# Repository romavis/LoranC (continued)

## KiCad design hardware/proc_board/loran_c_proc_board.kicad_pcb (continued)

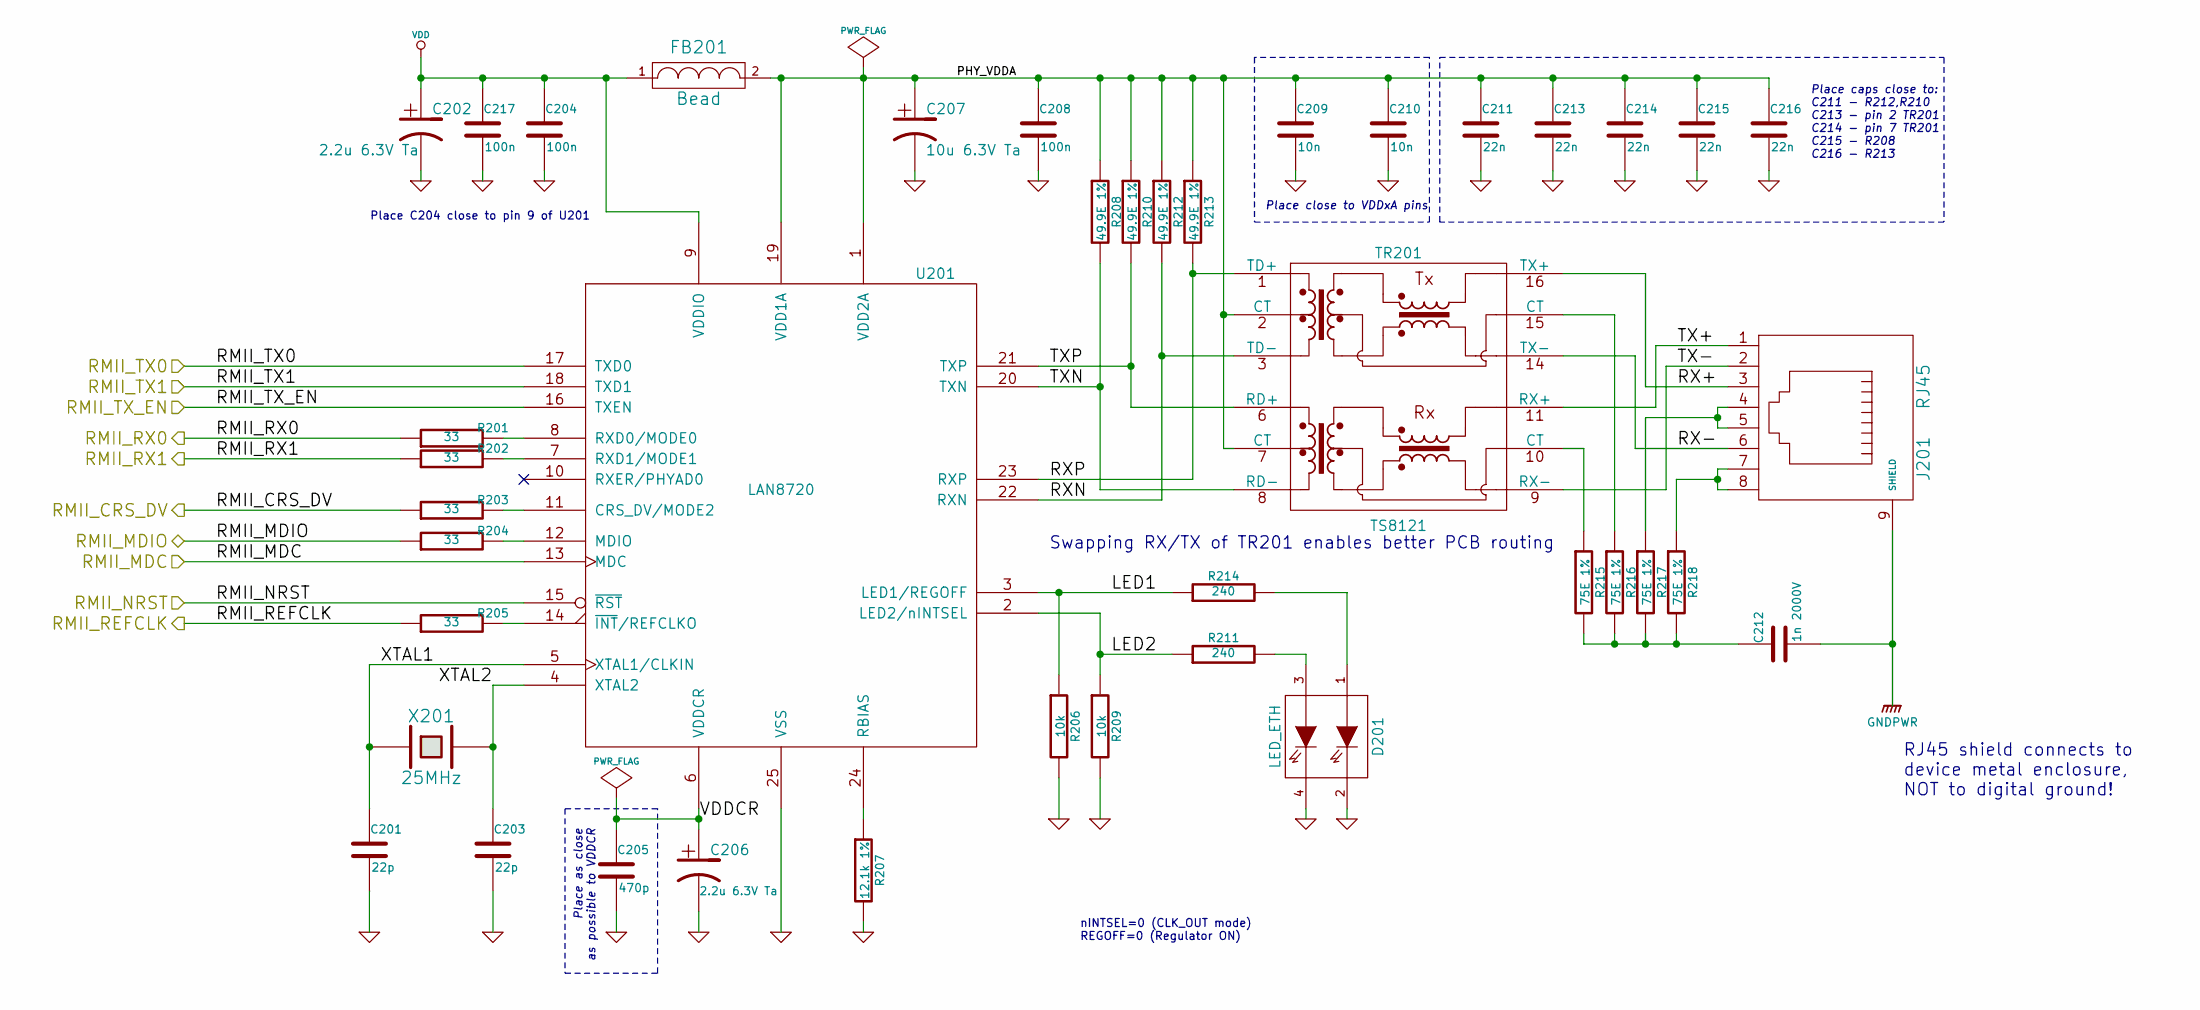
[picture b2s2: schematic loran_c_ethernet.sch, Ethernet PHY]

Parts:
C201, C203: 22p; r_0805
C202, C206: 2.2u 6.3V Ta; c_tant_A
C204, C208, C217: 100n; c_1206
C205: 470p; r_0805
C207: 10u 6.3V Ta; c_tant_B
C209, C210: 10n; c_1206
C211, C213, C214, C215, C216: 22n; c_1206
C212: 1n 2000V; cnp_6mm_disc
D201: LED_ETH
FB201: Bead; RC07
J201: RJ45; RJ45_8
R201, R202: 33; r_1206
R203, R204, R205: 33; r_0805
R206, R209: 10k; r_1206
R207: 12.1k 1%; r_1206
R208, R210, R212, R213: 49.9E 1%; r_1206
R211, R214: 240; r_1206
R215, R216, R217, R218: 75E 1%; r_1206
TR201: TS8121
U201: LAN8720; qfn-24
X201: 25MHz; crystal_hc-49u

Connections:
/Ethernet PHY/LED1: R206.1, R214.1, U201.3 (LED1/REGOFF)
/Ethernet PHY/LED2: R209.1, R211.1, U201.2 (LED2/nINTSEL)
/Ethernet PHY/PHY_VDDA: C207.1, C208.1, C209.1, C210.1, C211.1, C213.1, C214.1, C215.1, C216.1, FB201.2, R208.1, R210.1, R212.1, R213.1, TR201.2 (CT), TR201.7 (CT), U201.1 (VDD2A), U201.19 (VDD1A)
/Ethernet PHY/RMII_CRS_DV: R203.1; also elsewhere on the board
/Ethernet PHY/RMII_MDC: U201.13 (MDC); also elsewhere on the board
/Ethernet PHY/RMII_MDIO: R204.1; also elsewhere on the board
/Ethernet PHY/RMII_NRST: U201.15 (~RST); also elsewhere on the board
/Ethernet PHY/RMII_REFCLK: R205.1; also elsewhere on the board
/Ethernet PHY/RMII_RX0: R201.1; also elsewhere on the board
/Ethernet PHY/RMII_RX1: R202.1; also elsewhere on the board
/Ethernet PHY/RMII_TX0: U201.17 (TXD0); also elsewhere on the board
/Ethernet PHY/RMII_TX1: U201.18 (TXD1); also elsewhere on the board
/Ethernet PHY/RMII_TX_EN: U201.16 (TXEN); also elsewhere on the board
/Ethernet PHY/RX+: J201.3, TR201.16 (TX+)
/Ethernet PHY/RX-: J201.6, TR201.14 (TX-)
/Ethernet PHY/RXN: R212.2, TR201.3 (TD-), U201.22 (RXN)
/Ethernet PHY/RXP: R213.2, TR201.1 (TD+), U201.23 (RXP)
/Ethernet PHY/TX+: J201.1, TR201.11 (RX+)
/Ethernet PHY/TX-: J201.2, TR201.9 (RX-)
/Ethernet PHY/TXN: R208.2, TR201.8 (RD-), U201.20 (TXN)
/Ethernet PHY/TXP: R210.2, TR201.6 (RD+), U201.21 (TXP)
/Ethernet PHY/VDDCR: C205.1, C206.1, U201.6 (VDDCR)
/Ethernet PHY/XTAL1: C201.1, U201.5 (XTAL1/CLKIN), X201.1
/Ethernet PHY/XTAL2: C203.1, U201.4 (XTAL2), X201.2
GND: C201.2, C202.2, C203.2, C204.2, C205.2, C206.2, C207.2, C208.2, C209.2, C210.2, C211.2, C213.2, C214.2, C215.2, C216.2, C217.2, D201.2 (K1), D201.4 (K2), R206.2, R207.2, R209.2, U201.25 (VSS); also elsewhere on the board
GNDPWR: C212.2, J201.9 (SHIELD); also elsewhere on the board
unnamed: C212.1, R215.2, R216.2, R217.2, R218.2
unnamed: D201.1 (A1), R214.2
unnamed: D201.3 (A2), R211.2
unnamed: J201.4, J201.5, R217.1
unnamed: J201.7, J201.8, R218.1
unnamed: R201.2, U201.8 (RXD0/MODE0)
unnamed: R202.2, U201.7 (RXD1/MODE1)
unnamed: R203.2, U201.11 (CRS_DV/MODE2)
unnamed: R204.2, U201.12 (MDIO)
unnamed: R205.2, U201.14 (~INT~/REFCLKO)
unnamed: R207.1, U201.24 (RBIAS)
unnamed: R215.1, TR201.10 (CT)
unnamed: R216.1, TR201.15 (CT)
VDD: C202.1, C204.1, C217.1, FB201.1, U201.9 (VDDIO); also elsewhere on the board

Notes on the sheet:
nINTSEL=0 (CLK_OUT mode) REGOFF=0 (Regulator ON)
Place caps close to: C211 - R212,R210 C213 - pin 2 TR201 C214 - pin 7 TR201 C215 - R208 C216 - R213
Place as close as possible to VDDCR
Place close to VDDxA pins
RJ45 shield connects to device metal enclosure, NOT to digital ground!
Swapping RX/TX of TR201 enables better PCB routing
Place C204 close to pin 9 of U201

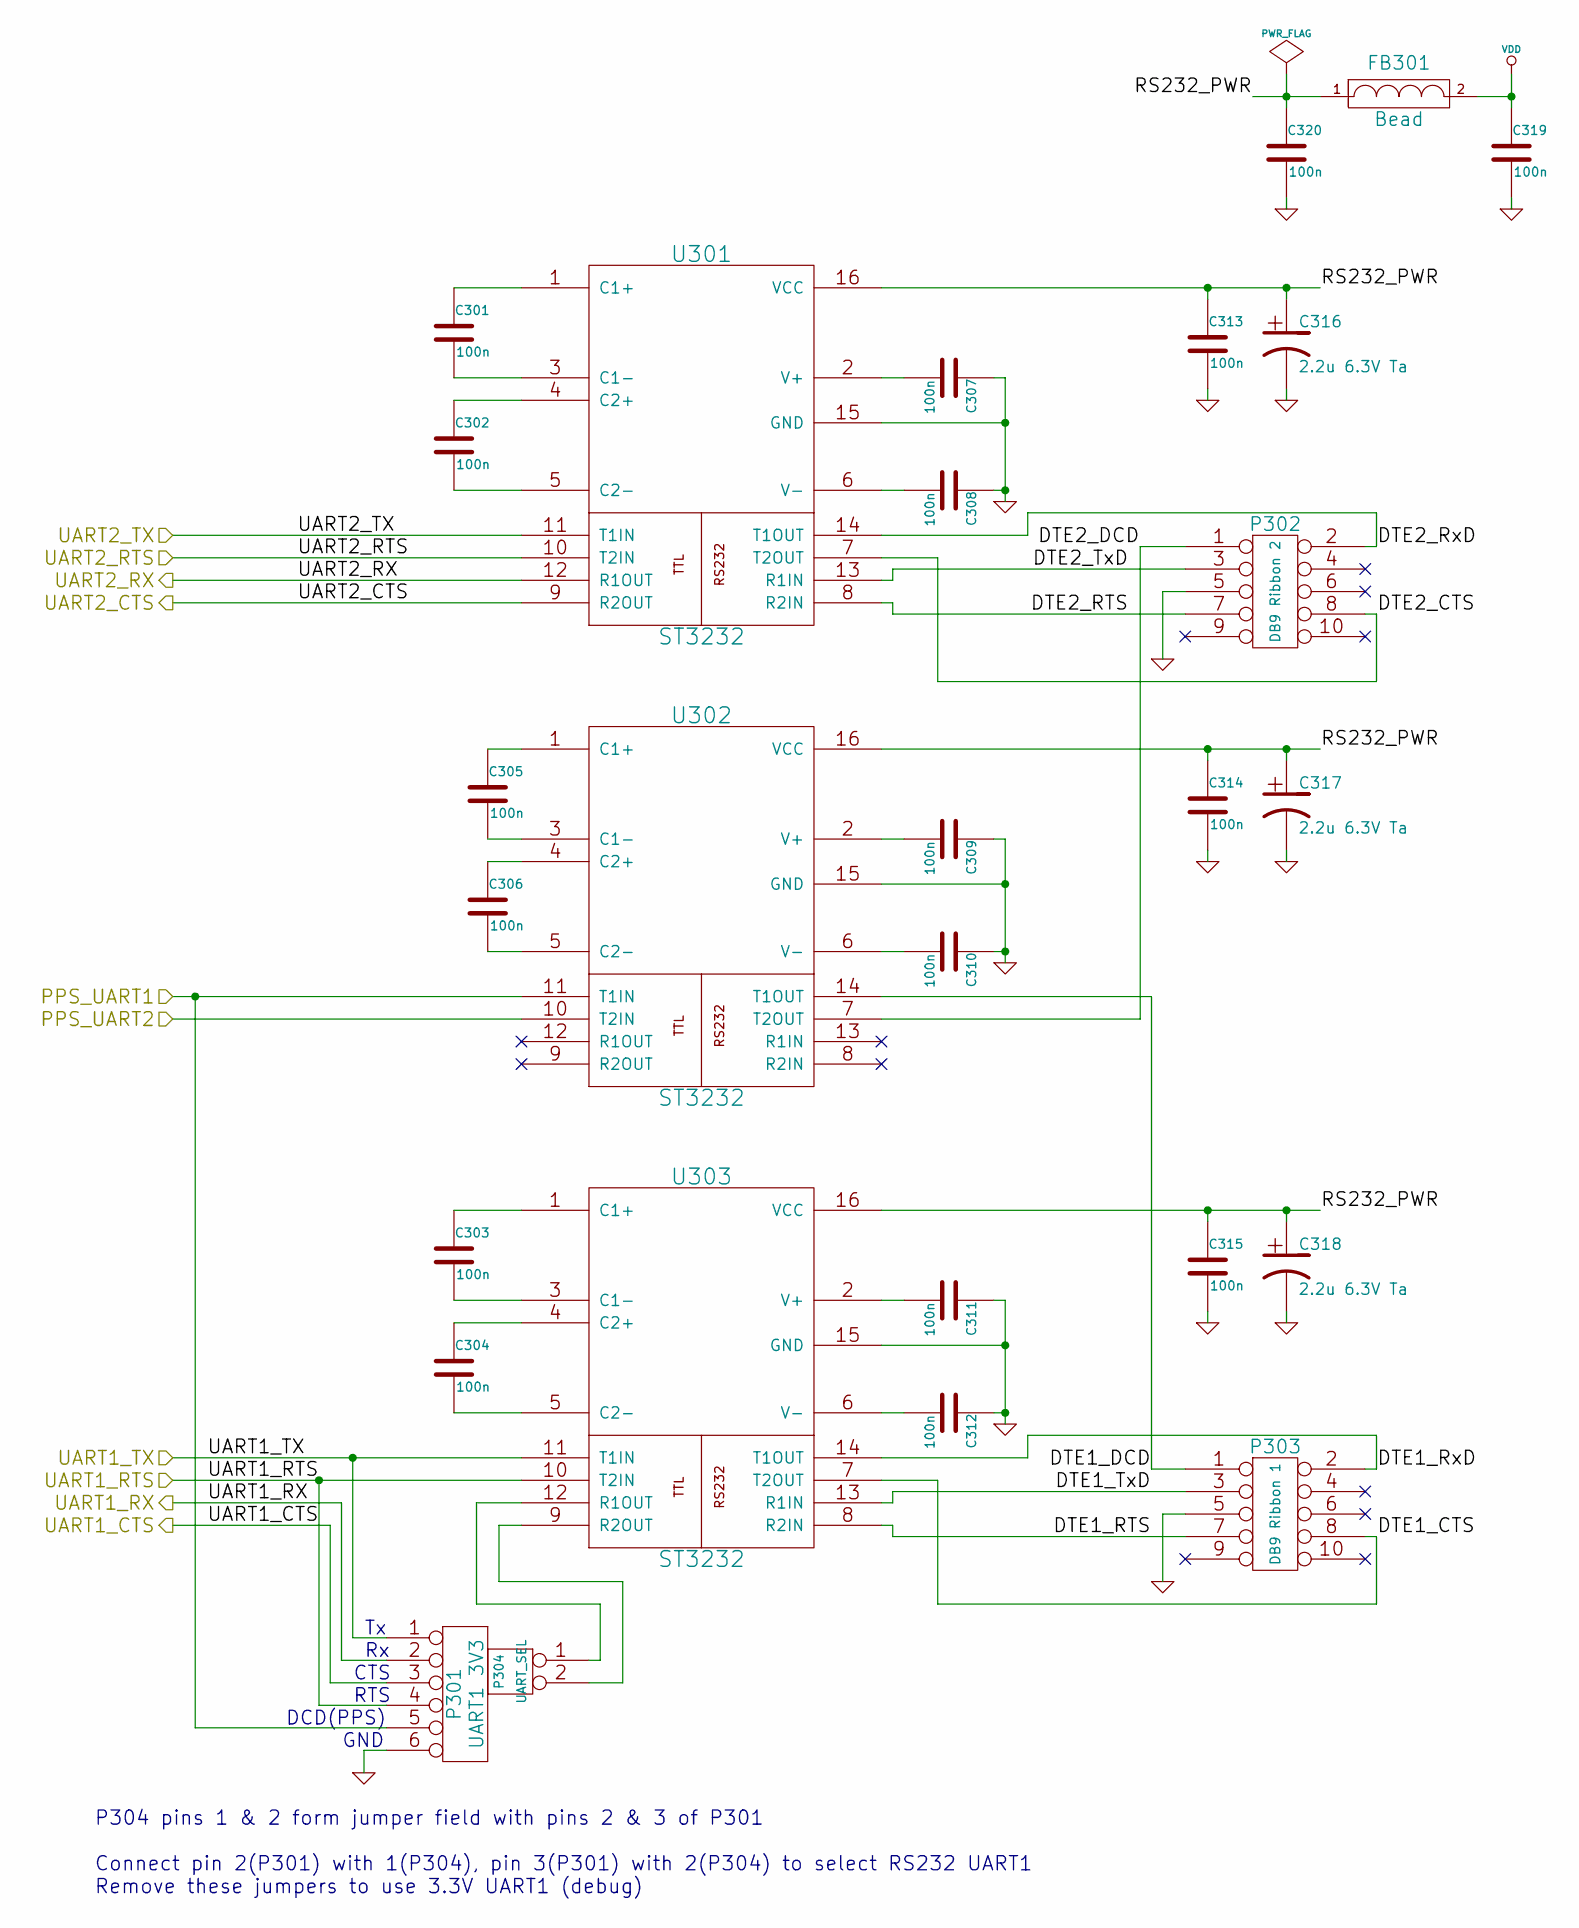
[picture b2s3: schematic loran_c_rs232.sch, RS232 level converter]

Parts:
C301, C302, C303, C304, C305, C306, C307, C308, C309, C310, C311, C312, C313, C314, C315, C319, C320: 100n; c_1206
C316, C317, C318: 2.2u 6.3V Ta; c_tant_A
FB301: Bead; RC07
P301: UART1 3V3; Pin_Header_Straight_1x06
P302: DB9 Ribbon 2; vasch_strip_5x2
P303: DB9 Ribbon 1; vasch_strip_5x2
P304: UART_SEL; Pin_Header_Straight_1x02
U301, U302, U303: ST3232; so-16

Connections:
/RS232 interface/DTE1_CTS: P303.8, U303.7 (T2OUT)
/RS232 interface/DTE1_DCD: P303.1, U302.14 (T1OUT)
/RS232 interface/DTE1_RTS: P303.7, U303.8 (R2IN)
/RS232 interface/DTE1_RxD: P303.2, U303.14 (T1OUT)
/RS232 interface/DTE1_TxD: P303.3, U303.13 (R1IN)
/RS232 interface/DTE2_CTS: P302.8, U301.7 (T2OUT)
/RS232 interface/DTE2_DCD: P302.1, U302.7 (T2OUT)
/RS232 interface/DTE2_RTS: P302.7, U301.8 (R2IN)
/RS232 interface/DTE2_RxD: P302.2, U301.14 (T1OUT)
/RS232 interface/DTE2_TxD: P302.3, U301.13 (R1IN)
/RS232 interface/RS232_PWR: C313.1, C314.1, C315.1, C316.1, C317.1, C318.1, C320.1, FB301.1, U301.16 (VCC), U302.16 (VCC), U303.16 (VCC)
/RS232 interface/UART1_CTS: P301.3; also elsewhere on the board
/RS232 interface/UART1_RTS: P301.4, U303.10 (T2IN); also elsewhere on the board
/RS232 interface/UART1_RX: P301.2; also elsewhere on the board
/RS232 interface/UART1_TX: P301.1, U303.11 (T1IN); also elsewhere on the board
/RS232 interface/UART2_CTS: U301.9 (R2OUT); also elsewhere on the board
/RS232 interface/UART2_RTS: U301.10 (T2IN); also elsewhere on the board
/RS232 interface/UART2_RX: U301.12 (R1OUT); also elsewhere on the board
/RS232 interface/UART2_TX: U301.11 (T1IN); also elsewhere on the board
/uC STM32F407/PPS1: P301.5, U302.11 (T1IN); also elsewhere on the board
/uC STM32F407/PPS2: U302.10 (T2IN); also elsewhere on the board
GND: C307.1, C308.1, C309.1, C310.1, C311.1, C312.1, C313.2, C314.2, C315.2, C316.2, C317.2, C318.2, C319.2, C320.2, P301.6, P302.5, P303.5, U301.15 (GND), U302.15 (GND), U303.15 (GND); also elsewhere on the board
unnamed: C301.1, U301.1 (C1+)
unnamed: C301.2, U301.3 (C1-)
unnamed: C302.1, U301.4 (C2+)
unnamed: C302.2, U301.5 (C2-)
unnamed: C303.1, U303.1 (C1+)
unnamed: C303.2, U303.3 (C1-)
unnamed: C304.1, U303.4 (C2+)
unnamed: C304.2, U303.5 (C2-)
unnamed: C305.1, U302.1 (C1+)
unnamed: C305.2, U302.3 (C1-)
unnamed: C306.1, U302.4 (C2+)
unnamed: C306.2, U302.5 (C2-)
unnamed: C307.2, U301.2 (V+)
unnamed: C308.2, U301.6 (V-)
unnamed: C309.2, U302.2 (V+)
unnamed: C310.2, U302.6 (V-)
unnamed: C311.2, U303.2 (V+)
unnamed: C312.2, U303.6 (V-)
unnamed: P304.1, U303.12 (R1OUT)
unnamed: P304.2 (PM), U303.9 (R2OUT)
VDD: C319.1, FB301.2; also elsewhere on the board

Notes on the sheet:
RTS
CTS
DCD(PPS)
GND
P304 pins 1 & 2 form jumper field with pins 2 & 3 of P301 Connect pin 2(P301) with 1(P304), pin 3(P301) with 2(P304) to select RS232 UART1 Remove these jumpers to use 3.3V UART1 (debug)

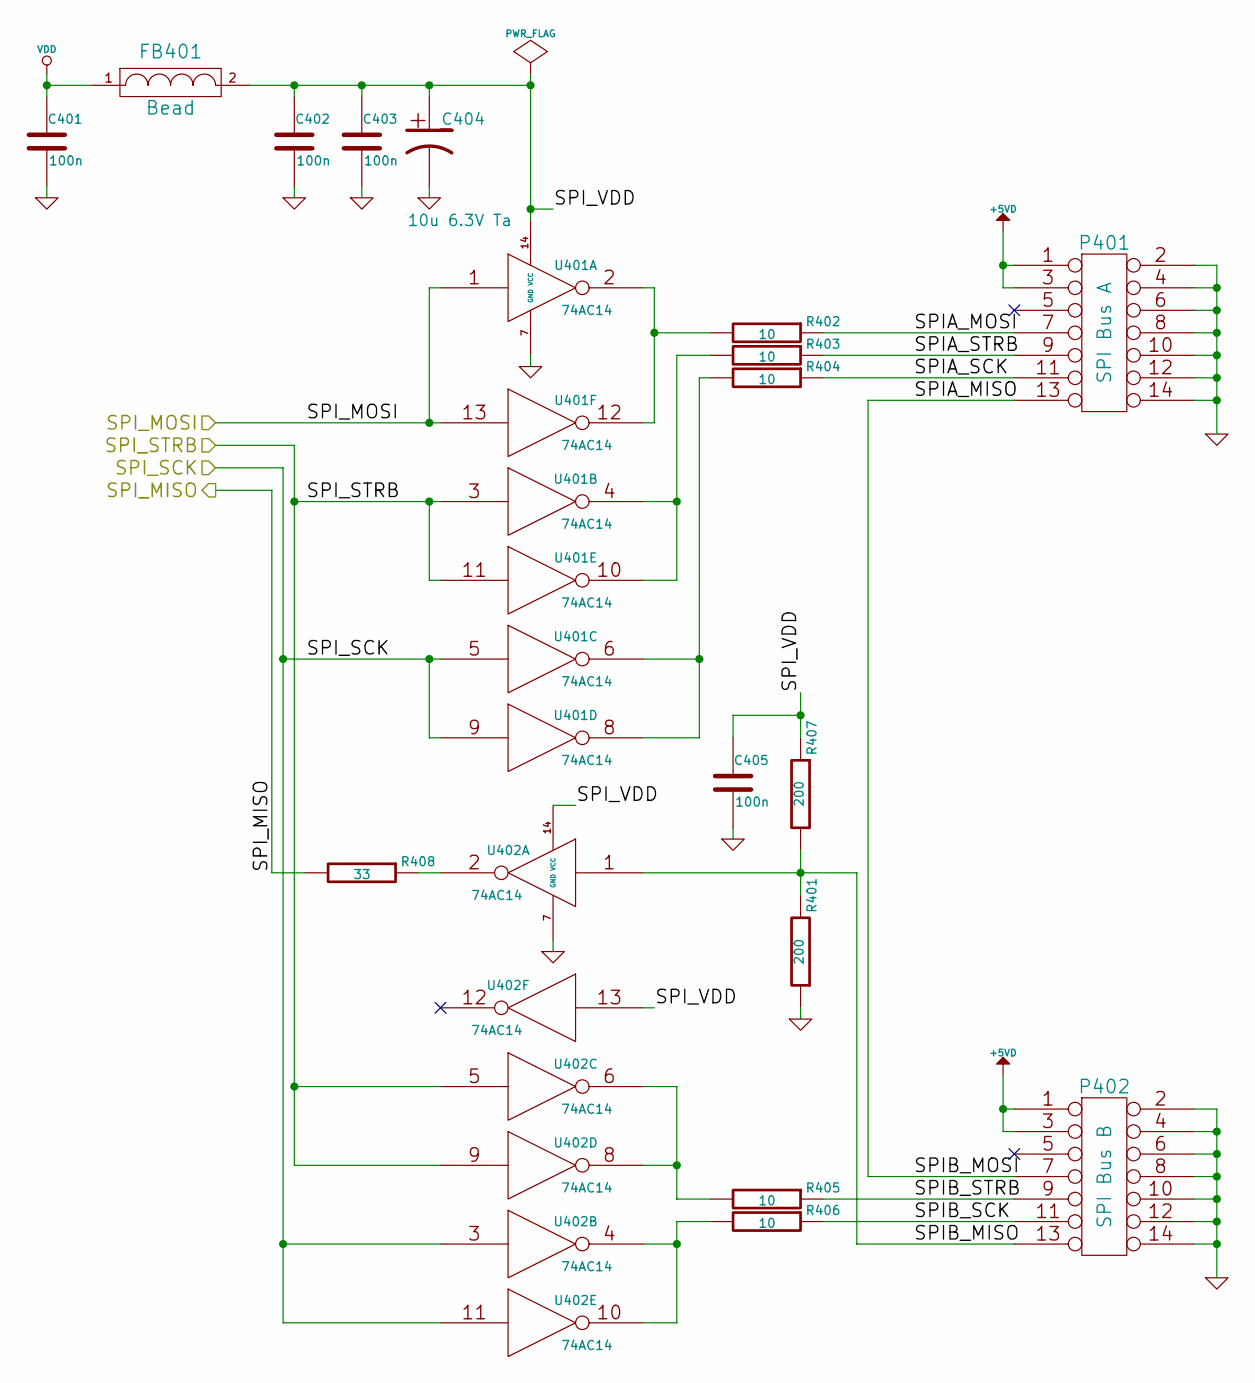
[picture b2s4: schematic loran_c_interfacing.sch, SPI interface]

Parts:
C401, C402, C403, C405: 100n; c_1206
C404: 10u 6.3V Ta; c_tant_B
FB401: Bead; RC07
P401: SPI Bus A; vasch_strip_7x2
P402: SPI Bus B; vasch_strip_7x2
R401, R407: 200; r_1206
R402, R403, R404, R405, R406: 10; r_1206
R408: 33; r_1206
U401, U402: 74AC14; so-14

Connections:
+5VD: P401.1, P401.3, P402.1, P402.3; also elsewhere on the board
/SPI interface/SPIA_MISO: P401.13, P402.7
/SPI interface/SPIA_MOSI: P401.7, R402.1
/SPI interface/SPIA_SCK: P401.11, R404.1
/SPI interface/SPIA_STRB: P401.9, R403.1
/SPI interface/SPIB_MISO: P402.13, R401.2, R407.2, U402.1
/SPI interface/SPIB_SCK: P402.11, R406.1
/SPI interface/SPIB_STRB: P402.9, R405.1
/SPI interface/SPI_MISO: R408.2; also elsewhere on the board
/SPI interface/SPI_MOSI: U401.1, U401.13; also elsewhere on the board
/SPI interface/SPI_SCK: U401.5, U401.9, U402.3, U402.11; also elsewhere on the board
/SPI interface/SPI_STRB: U401.3, U401.11, U402.5, U402.9; also elsewhere on the board
/SPI interface/SPI_VDD: C402.1, C403.1, C404.1, C405.1, FB401.2, R407.1, U401.14 (VCC), U402.13, U402.14 (VCC)
GND: C401.2, C402.2, C403.2, C404.2, C405.2, P401.2, P401.4, P401.6, P401.8, P401.10, P401.12, P401.14, P402.2, P402.4, P402.6, P402.8, P402.10, P402.12, P402.14, R401.1, U401.7 (GND), U402.7 (GND); also elsewhere on the board
unnamed: R402.2, U401.2, U401.12
unnamed: R403.2, U401.4, U401.10
unnamed: R404.2, U401.6, U401.8
unnamed: R405.2, U402.6, U402.8
unnamed: R406.2, U402.4, U402.10
unnamed: R408.1, U402.2
VDD: C401.1, FB401.1; also elsewhere on the board

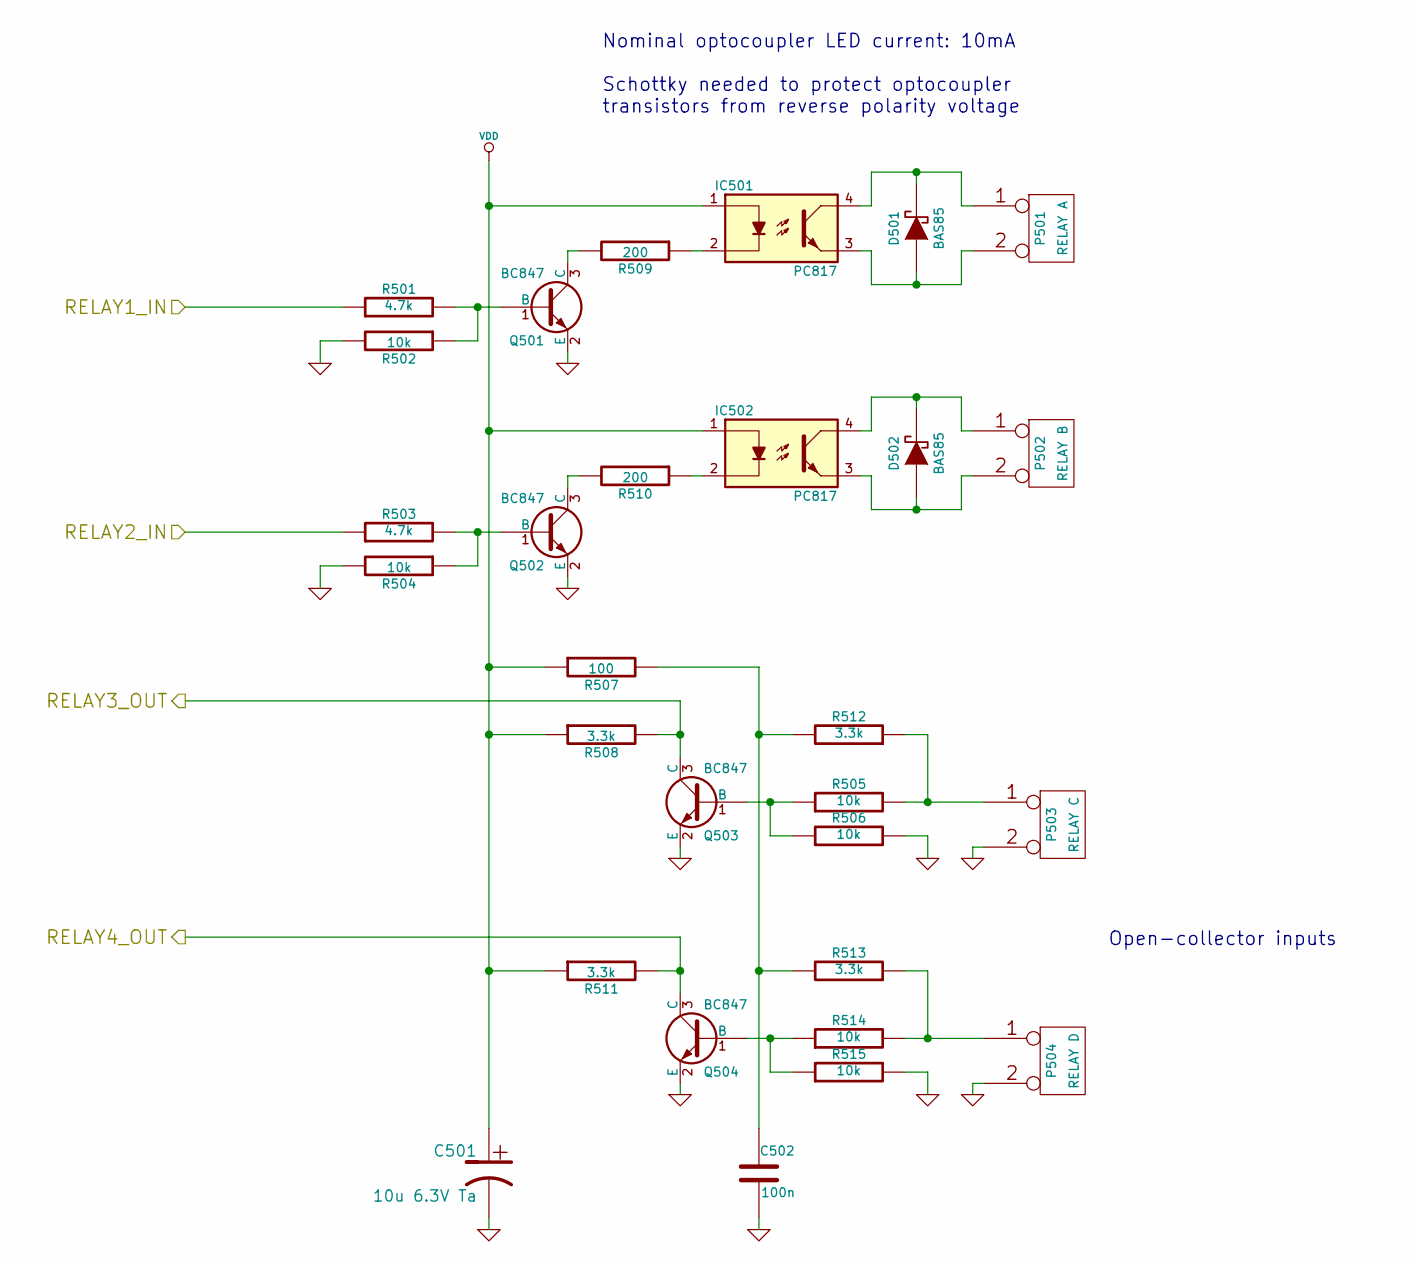
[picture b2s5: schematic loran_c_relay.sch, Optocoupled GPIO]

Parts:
C501: 10u 6.3V Ta; c_tant_B
C502: 100n; c_1206
D501, D502: BAS85; sod80c
IC501, IC502: PC817; dil_4-300
P501: RELAY A; kk100_22-23-2021
P502: RELAY B; kk100_22-23-2021
P503: RELAY C; kk100_22-23-2021
P504: RELAY D; kk100_22-23-2021
Q501, Q502, Q503, Q504: BC847; SOT23
R501, R503: 4.7k; r_1206
R502, R504, R505, R506, R514, R515: 10k; r_1206
R507: 100; r_1206
R508, R511, R512, R513: 3.3k; r_1206
R509, R510: 200; r_1206

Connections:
/uC STM32F407/RELAY1: R501.1; also elsewhere on the board
/uC STM32F407/RELAY2: R503.1; also elsewhere on the board
/uC STM32F407/RELAY3: Q503.3 (C), R508.2; also elsewhere on the board
/uC STM32F407/RELAY4: Q504.3 (C), R511.2; also elsewhere on the board
GND: C501.2, C502.2, P503.2 (PM), P504.2 (PM), Q501.2 (E), Q502.2 (E), Q503.2 (E), Q504.2 (E), R502.2, R504.2, R506.2, R515.2; also elsewhere on the board
unnamed: C502.1, R507.2, R512.2, R513.2
unnamed: D501.1 (A), IC501.3, P501.2 (PM)
unnamed: D501.2 (K), IC501.4, P501.1
unnamed: D502.1 (A), IC502.3, P502.2 (PM)
unnamed: D502.2 (K), IC502.4, P502.1
unnamed: IC501.2, R509.1
unnamed: IC502.2, R510.1
unnamed: P503.1, R505.2, R512.1
unnamed: P504.1, R513.1, R514.2
unnamed: Q501.1 (B), R501.2, R502.1
unnamed: Q501.3 (C), R509.2
unnamed: Q502.1 (B), R503.2, R504.1
unnamed: Q502.3 (C), R510.2
unnamed: Q503.1 (B), R505.1, R506.1
unnamed: Q504.1 (B), R514.1, R515.1
VDD: C501.1, IC501.1, IC502.1, R507.1, R508.1, R511.1; also elsewhere on the board

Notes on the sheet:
Nominal optocoupler LED current: 10mA Schottky needed to protect optocoupler transistors from reverse polarity voltage
Open-collector inputs

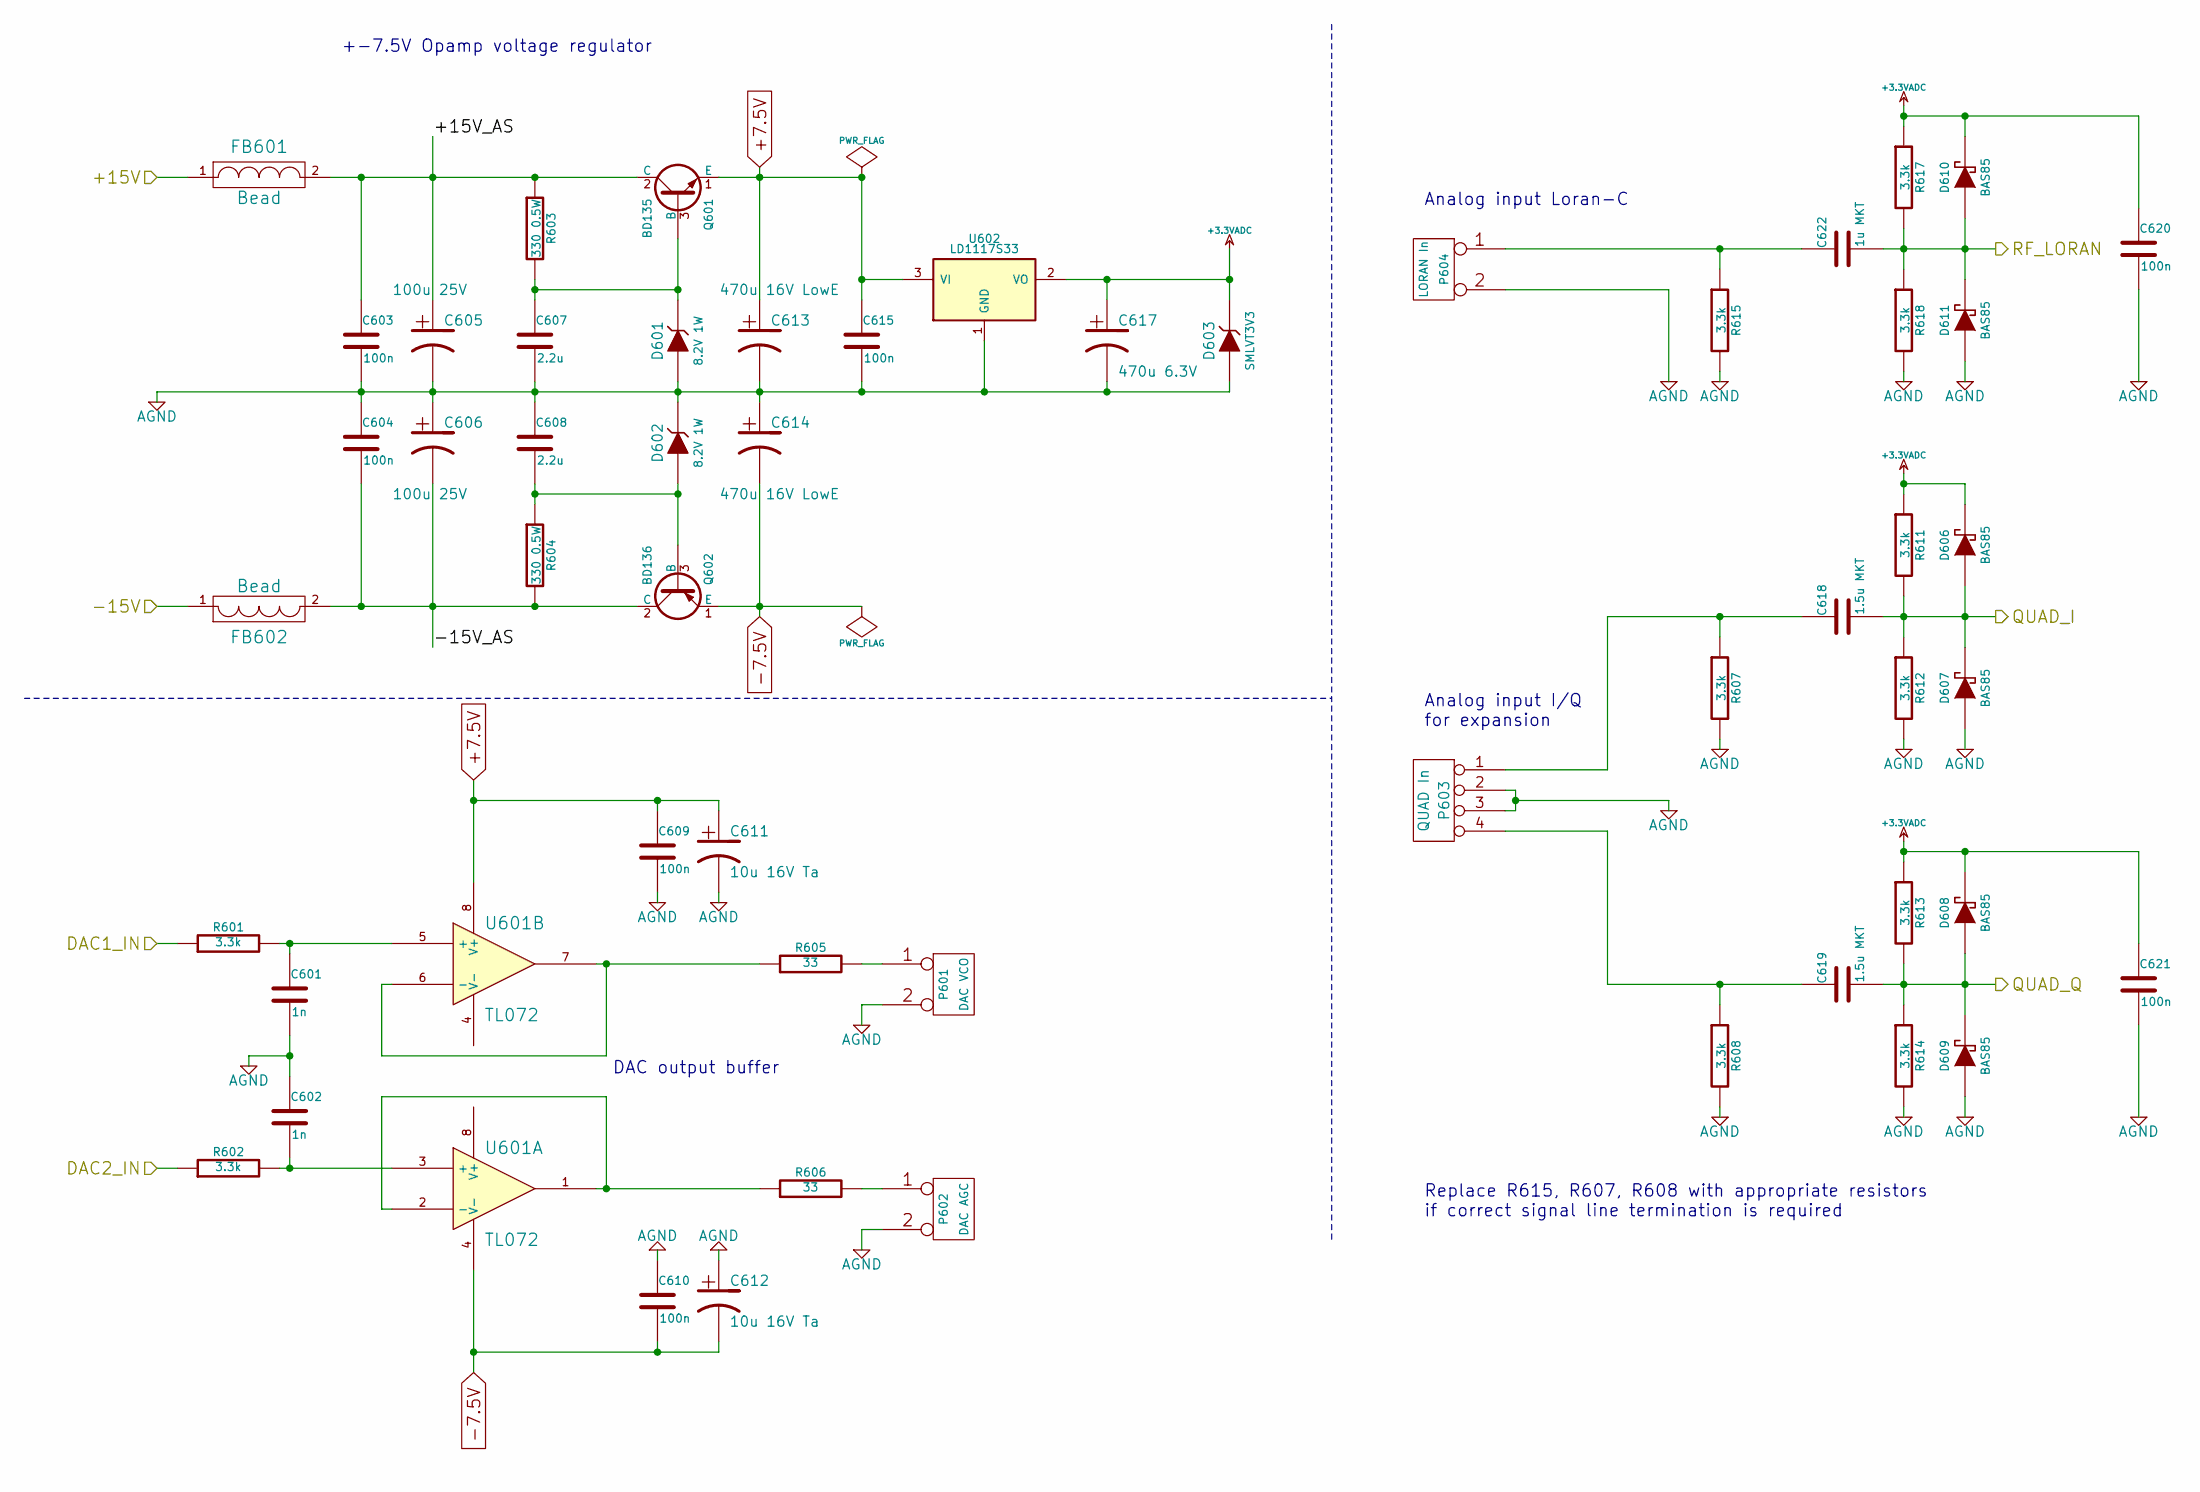
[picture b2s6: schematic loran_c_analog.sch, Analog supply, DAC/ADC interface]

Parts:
C601, C602: 1n; c_1206
C603, C604, C609, C610, C615, C620, C621: 100n; c_1206
C605, C606: 100u 25V; CP_6.3x11mm
C607, C608: 2.2u; c_1206
C611, C612: 10u 16V Ta; c_tant_B
C613, C614: 470u 16V LowE; CP_10x12.5mm
C617: 470u 6.3V; CP_6.3x11mm
C618, C619: 1.5u MKT; cnp_7x6mm
C622: 1u MKT; cnp_7x6mm
D601, D602: 8.2V 1W; diode_do41
D603: SMLVT3V3; do214aa
D606, D607, D608, D609, D610, D611: BAS85; sod80c
FB601, FB602: Bead; RC07
P601: DAC VCO; kk100_22-23-2021
P602: DAC AGC; kk100_22-23-2021
P603: QUAD In; kk100_22-23-2041
P604: LORAN In; kk100_22-23-2021
Q601: BD135; SOT126_SOT32_Housing_Vertical_BigPads
Q602: BD136; SOT126_SOT32_Housing_Vertical_BigPads
R601, R602, R607, R608, R611, R612, R613, R614, R615, R617, R618: 3.3k; r_1206
R603, R604: 330 0.5W; RC05
R605, R606: 33; r_0805
U601: TL072; so-8
U602: LD1117S33; SOT223

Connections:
+3.3VADC: C617.1, C620.1, C621.1, D603.2 (K), D606.2 (K), D608.2 (K), D610.2 (K), R611.1, R613.1, R617.1, U602.2 (VO); also elsewhere on the board
+7.5V: C609.1, C611.1, C613.1, C615.1, Q601.1 (E), U601.8 (V+), U602.3 (VI)
-7.5V: C610.2, C612.2, C614.2, Q602.1 (E), U601.4 (V-)
/Analog part/+15V: FB601.1; also elsewhere on the board
/Analog part/+15V_AS: C603.1, C605.1, FB601.2, Q601.2 (C), R603.1
/Analog part/-15V: FB602.1; also elsewhere on the board
/Analog part/-15V_AS: C604.2, C606.2, FB602.2, Q602.2 (C), R604.2
/Analog part/DAC1_IN: R601.1; also elsewhere on the board
/Analog part/DAC2_IN: R602.1; also elsewhere on the board
/uC STM32F407/ADC1_IN: C619.2, D608.1 (A), D609.2 (K), R613.2, R614.1; also elsewhere on the board
/uC STM32F407/ADC2_IN: C618.2, D606.1 (A), D607.2 (K), R611.2, R612.1; also elsewhere on the board
/uC STM32F407/ADC3_IN: C622.2, D610.1 (A), D611.2 (K), R617.2, R618.1; also elsewhere on the board
AGND: C601.2, C602.1, C603.2, C604.1, C605.2, C606.1, C607.2, C608.1, C609.2, C610.1, C611.2, C612.1, C613.2, C614.1, C615.2, C617.2, C620.2, C621.2, D601.1 (A), D602.2 (K), D603.1 (A), D607.1 (A), D609.1 (A), D611.1 (A), P601.2 (PM), P602.2 (PM), P603.2, P603.3, P604.2 (PM), R607.2, R608.2, R612.2, R614.2, R615.2, R618.2, U602.1 (GND); also elsewhere on the board
unnamed: C601.1, R601.2, U601.5 (+)
unnamed: C602.2, R602.2, U601.3 (+)
unnamed: C607.1, D601.2 (K), Q601.3 (B), R603.2
unnamed: C608.2, D602.1 (A), Q602.3 (B), R604.1
unnamed: C618.1, P603.1, R607.1
unnamed: C619.1, P603.4, R608.1
unnamed: C622.1, P604.1, R615.1
unnamed: P601.1, R605.2
unnamed: P602.1, R606.2
unnamed: R605.1, U601.6 (-), U601.7
unnamed: R606.1, U601.1, U601.2 (-)

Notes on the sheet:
DAC output buffer
+-7.5V Opamp voltage regulator
Analog input I/Q for expansion
Analog input Loran-C
Replace R615, R607, R608 with appropriate resistors if correct signal line termination is required
